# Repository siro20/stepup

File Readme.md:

# Non-isolated 12V to 120V boost converter

This project is about finding a power supply to drive regular 240V/120V
LED bulbs from a 12V power supply or 12V battery.

This is the first prototype build using the [LM3478](https://www.ti.com/product/de-de/LM3478).

It features:
- Up to 36 Watts
- Inrush current limit
- LC input filter
- Follows TI's reference design

## Analysis

The boost converter was found working and it outputs 120VDC.

**WARNING**: The project was abadonned due to the undocumented behaviour of the LM3478!

- The LM3478 has no soft-start mechanism.
- The LM3478 starts to operate at 3V at Vin
- The LM3478 gate drive voltage is quite low with 7.2V or less

**At startup the LM3478 doesn't operate at all. It just pulls the gate drive high and
waits for an over-current condition. Once the over-current conditions happens it
starts operating in PWM mode.**

**The board draws more than 40Watts without starting to switch the Mosfet as the current
limit isn't reached.**

## kicad board files

The PCB has dimensions of 32mmx82mm:

The schematic [available as PDF here](schematics/stepup.pdf) is following the reference design:

## Disclaimer

    THE OPEN SOURCE SOFTWARE/HARDWARE IN THIS PROJECT IS DISTRIBUTED
    IN THE HOPE THAT IT WILL BE USEFUL, BUT WITHOUT ANY WARRANTY, WITHOUT
    EVEN THE IMPLIED WARRANTY OF MERCHANTABILITY OR FITNESS FOR A
    PARTICULAR PURPOSE.

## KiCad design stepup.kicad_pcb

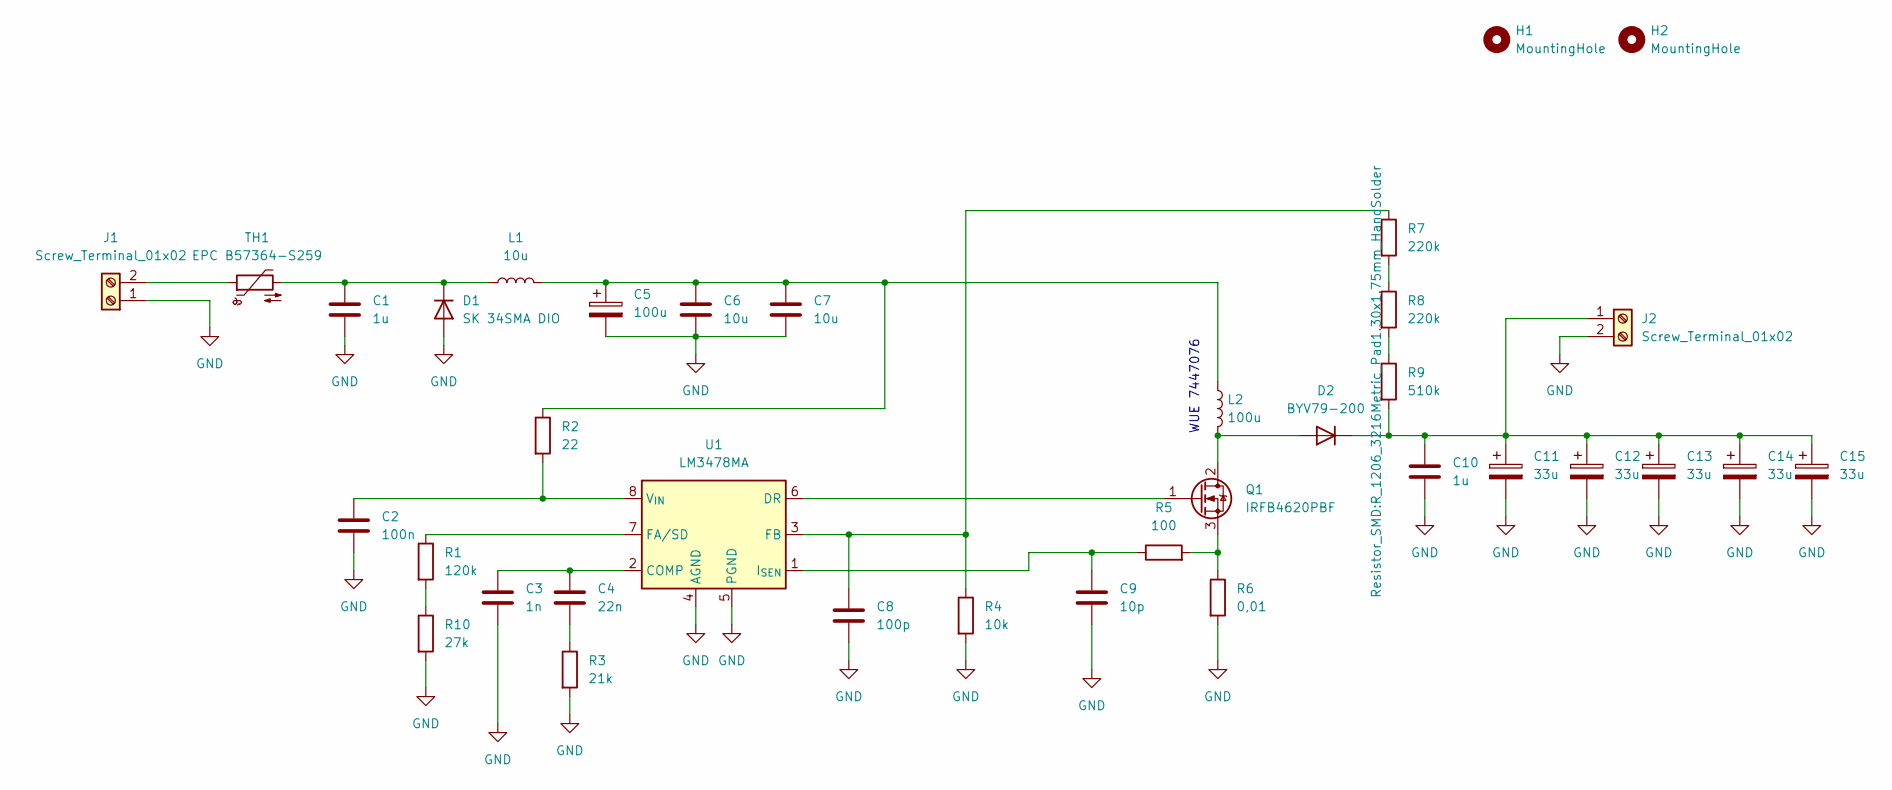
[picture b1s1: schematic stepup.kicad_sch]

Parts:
C1: 1u; R_0805_2012Metric_Pad1.20x1.40mm_HandSolder
C2: 100n; C_0805_2012Metric_Pad1.18x1.45mm_HandSolder
C3: 1n; C_0603_1608Metric_Pad1.08x0.95mm_HandSolder
C4: 22n; C_0603_1608Metric_Pad1.08x0.95mm_HandSolder
C5: 100u; C_Radial_D8.0mm_H11.5mm_P3.50mm
C6, C7: 10u; R_1210_3225Metric_Pad1.30x2.65mm_HandSolder
C8: 100p; C_0603_1608Metric_Pad1.08x0.95mm_HandSolder
C9: 10p; C_0603_1608Metric_Pad1.08x0.95mm_HandSolder
C10: 1u; C_Rect_L18.0mm_W7.0mm_P15.00mm_FKS3_FKP3
C11, C12, C13, C14, C15: 33u; C_Radial_D10.0mm_H20.0mm_P5.00mm
D1: SK 34SMA DIO; D_SMA
D2: BYV79-200; TO-220-2_Vertical
H1, H2: MountingHole; MountingHole_2.7mm_M2.5
J1, J2: Screw_Terminal_01x02; TerminalBlock_Phoenix_PT-1,5-2-3.5-H_1x02_P3.50mm_Horizontal
L1: 10u; L_Toroid_Vertical_L16.4mm_W7.6mm_P6.60mm_Vishay_TJ3
L2: 100u; L_Toroid_Vertical_L26.7mm_W14.0mm_P10.16mm_Pulse_D
Q1: IRFB4620PBF; TO-220-3_Vertical
R1: 120k; R_0805_2012Metric_Pad1.20x1.40mm_HandSolder
R2: 22; R_0805_2012Metric_Pad1.20x1.40mm_HandSolder
R3: 21k; R_0805_2012Metric_Pad1.20x1.40mm_HandSolder
R4: 10k; R_0805_2012Metric_Pad1.20x1.40mm_HandSolder
R5: 100; R_0805_2012Metric_Pad1.20x1.40mm_HandSolder
R6: 0,01; R_1206_3216Metric_Pad1.30x1.75mm_HandSolder
R7, R8: 220k; R_1206_3216Metric_Pad1.30x1.75mm_HandSolder
R9: 510k; R_1206_3216Metric_Pad1.30x1.75mm_HandSolder
R10: 27k; R_0805_2012Metric_Pad1.20x1.40mm_HandSolder
TH1: EPC B57364-S259; R_Axial_Power_L20.0mm_W6.4mm_P7.62mm_Vertical
U1: LM3478MA; SOIC-8_3.9x4.9mm_P1.27mm

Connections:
GND: C1.2, C2.2, C3.2, C5.2, C6.2, C7.2, C8.2, C9.2, C10.2, C11.2, C12.2, C13.2, C14.2, C15.2, D1.2 (A), J1.1, J2.2, R3.2, R4.2, R6.2, R10.2, U1.4 (AGND), U1.5 (PGND)
unnamed: C1.1, D1.1 (K), L1.1, TH1.2
unnamed: C2.1, R2.2, U1.8 (V_{IN})
unnamed: C3.1, C4.1, U1.2 (COMP)
unnamed: C4.2, R3.1
unnamed: C5.1, C6.1, C7.1, L1.2, L2.1, R2.1
unnamed: C8.1, R4.1, R7.1, U1.3 (FB)
unnamed: C9.1, R5.1, U1.1 (I_{SEN})
unnamed: C10.1, C11.1, C12.1, C13.1, C14.1, C15.1, D2.1 (K), J2.1, R9.2
unnamed: D2.2 (A), L2.2, Q1.2 (D)
unnamed: J1.2, TH1.1
unnamed: Q1.1 (G), U1.6 (DR)
unnamed: Q1.3 (S), R5.2, R6.1
unnamed: R1.1, U1.7 (FA/SD)
unnamed: R1.2, R10.1
unnamed: R7.2, R8.1
unnamed: R8.2, R9.1

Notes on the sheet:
WUE 7447076

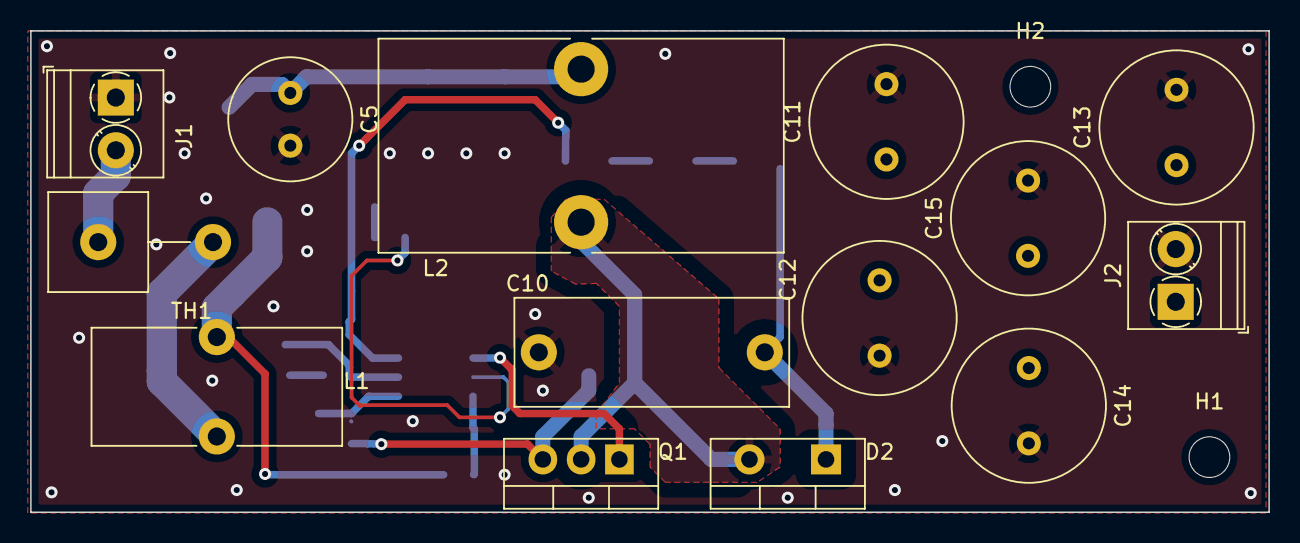
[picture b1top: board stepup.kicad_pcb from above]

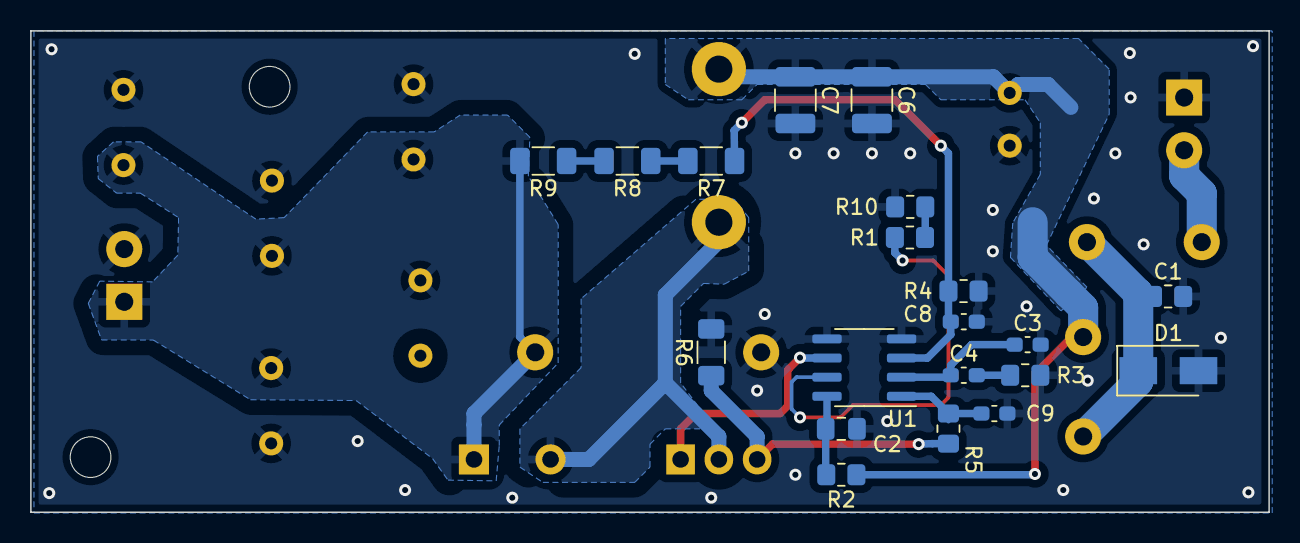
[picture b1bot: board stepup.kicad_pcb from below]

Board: 2 copper layers, 82.2 x 32.0 mm, 36 parts (20 on the bottom side), 17 nets.

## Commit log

2023-04-05 Readme: Update schematics folder
